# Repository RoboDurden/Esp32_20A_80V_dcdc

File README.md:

# Esp32_20A_80V_dcdc
 20A 80V dcdc/mppt with Esp32 and touch display

## KiCad pcb

## replaces lcd pickup module

https://www.aliexpress.com/item/1005004966830126.html

## KiCad circuit

## blender 3d models

## blender box / housing

## Arduino code (ssd1306)

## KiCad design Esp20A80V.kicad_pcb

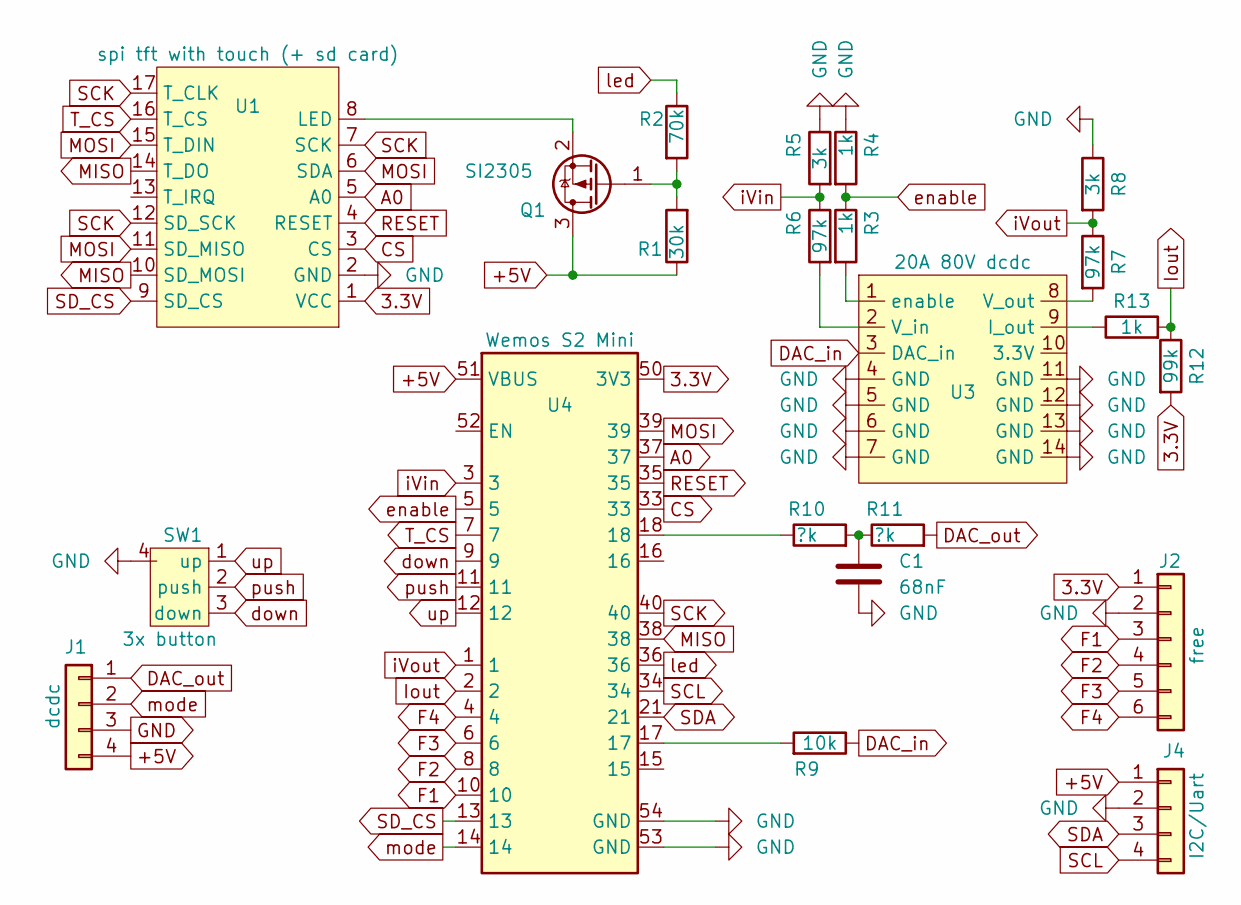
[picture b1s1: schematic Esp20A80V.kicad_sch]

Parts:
C1: 68nF; C_0805_2012Metric_Pad1.18x1.45mm_HandSolder
J1: dcdc; JST_PH_B4B-PH-K_1x04_P2.00mm_Vertical
J2: free; PinHeader_1x06_P2.54mm_Horizontal
J4: I2C/Uart; PinHeader_1x04_P2.54mm_Horizontal
Q1: SI2305; SOT-23
R1: 30k; R_0805_2012Metric_Pad1.20x1.40mm_HandSolder
R2: 70k; R_0805_2012Metric_Pad1.20x1.40mm_HandSolder
R3, R4, R13: 1k; R_0805_2012Metric_Pad1.20x1.40mm_HandSolder
R5, R8: 3k; R_0805_2012Metric_Pad1.20x1.40mm_HandSolder
R6, R7: 97k; R_0805_2012Metric_Pad1.20x1.40mm_HandSolder
R9: 10k; R_0805_2012Metric_Pad1.20x1.40mm_HandSolder
R10, R11: ?k; R_0805_2012Metric_Pad1.20x1.40mm_HandSolder
R12: 99k; R_0805_2012Metric_Pad1.20x1.40mm_HandSolder
SW1: 3x button; 3way dial switch
U1: spi tft with touch (+ sd card); display 128x160 +touch +sd
U3: 20A 80V dcdc; 20A80V dcdc
U4: Wemos S2 Mini

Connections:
3.3V: J2.1, R12.2, U1.1 (VCC), U4.50 (3V3)
+5V: J1.4, J4.1, Q1.3 (D), R1.1, U4.51 (VBUS)
A0: U1.5 (A0), U4.37
CS: U1.3 (CS), U4.33
DAC_in: R9.1, U3.3 (DAC_in)
DAC_out: J1.1, R11.2
F1: J2.3, U4.10
F2: J2.4, U4.8
F3: J2.5, U4.6
F4: J2.6, U4.4
GND: C1.2, J1.3, J2.2, J4.2, R4.1, R5.1, R8.1, SW1.4, U1.2 (GND), U3.4 (GND), U3.5 (GND), U3.6 (GND), U3.7 (GND), U3.11 (GND), U3.12 (GND), U3.13 (GND), U3.14 (GND), U4.53 (GND), U4.54 (GND)
Iout: R12.1, R13.2, U4.2
MISO: U1.10 (SD_MOSI), U1.14 (T_DO), U4.38
MOSI: U1.6 (SDA), U1.11 (SD_MISO), U1.15 (T_DIN), U4.39
unnamed: C1.1, R10.2, R11.1
unnamed: Q1.1 (G), R1.2, R2.2
unnamed: Q1.2 (S), U1.8 (LED)
unnamed: R9.2, U4.17
unnamed: R10.1, U4.18
unnamed: R13.1, U3.9 (I_out)
unnamed: R6.2, U3.2 (V_in)
unnamed: R7.2, U3.8 (V_out)
unnamed: R3.2, U3.1 (enable)
RESET: U1.4 (RESET), U4.35
SCK: U1.7 (SCK), U1.12 (SD_SCK), U1.17 (T_CLK), U4.40
SCL: J4.4, U4.34
SDA: J4.3, U4.21
SD_CS: U1.9 (SD_CS), U4.13
T_CS: U1.16 (T_CS), U4.7
down: SW1.3 (down), U4.9
enable: R3.1, R4.2, U4.5
iVin: R5.2, R6.1, U4.3
iVout: R7.1, R8.2, U4.1
led: R2.1, U4.36
mode: J1.2, U4.14
push: SW1.2 (push), U4.11
up: SW1.1 (up), U4.12

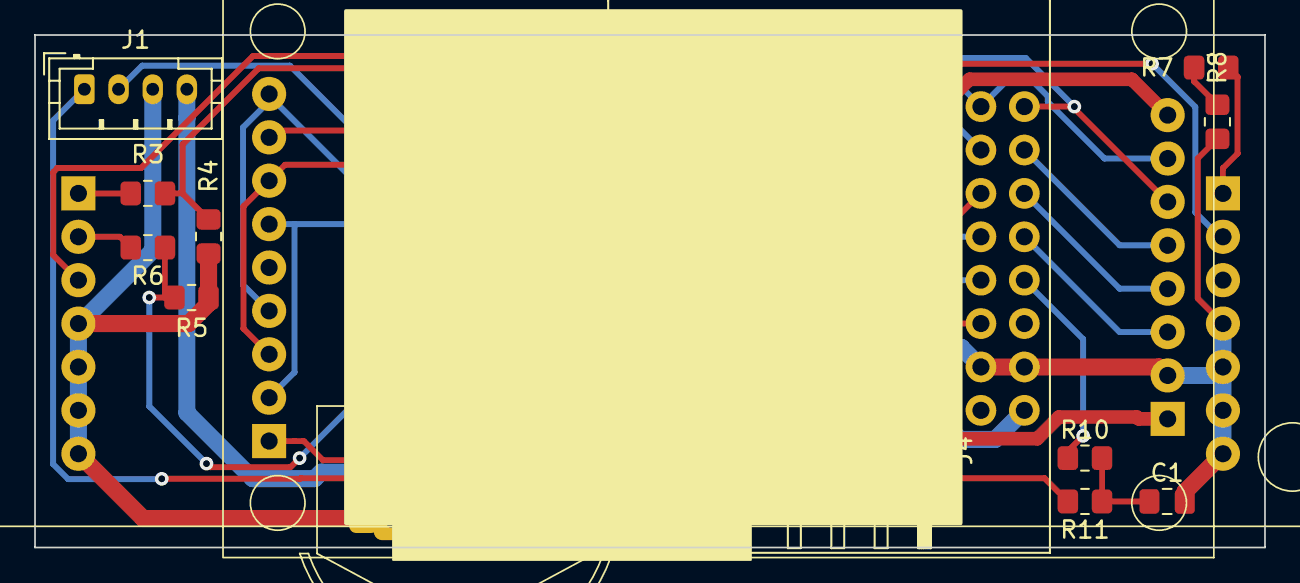
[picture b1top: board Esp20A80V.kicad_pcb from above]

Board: 2 copper layers, 72.0 x 30.0 mm, 22 parts (0 on the bottom side), 37 nets.

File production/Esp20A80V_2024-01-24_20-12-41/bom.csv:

Designator,Footprint,Quantity,Value,LCSC Part #
C1,0805,1,68nF,
J1,JST_PH_B4B-PH-K_1x04_P2.00mm_Vertical,1,dcdc,
J2,PinHeader_1x06_P2.54mm_Horizontal,1,free,
J4,PinHeader_1x04_P2.54mm_Horizontal,1,I2C/Uart,
Q1,SOT-23,1,SI2305,
R1,0805,1,30k,
"R10, R11",0805,2,?k,
R12,0805,1,99k,
"R13, R3, R4",0805,3,1k,
R2,0805,1,70k,
"R5, R8",0805,2,3k,
"R6, R7",0805,2,97k,
R9,0805,1,10k,
SW1,3way dial switch,1,3x button,
U1,display 128x160 +touch +sd,1,spi tft with touch (+ sd card),
U3,20A80V dcdc,1,20A 80V dcdc,
U4,Wemos S2 Mini,1,Wemos S2 Mini,

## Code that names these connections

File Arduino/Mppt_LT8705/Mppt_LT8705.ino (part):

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  pinMode(LED_BUILTIN, OUTPUT);

  pinMode(PIN_Uout,INPUT);
  pinMode(PIN_Iout,INPUT);

  //pinMode(PIN_DACin,INPUT);   // to not set an output hi or low level but analogOut
  
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
  pinMode(pin_Left, INPUT_PULLUP);
  pinMode(pin_Right, INPUT_PULLUP);
  pinMode(pin_Push, INPUT_PULLUP);

 
  // initialize digital pin LED_BUILTIN as an output.
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
  if (!digitalRead(pin_Left)) wButtons |= _ButtonDown;
  if (!digitalRead(pin_Right)) wButtons |= _ButtonUp;
  if (!digitalRead(pin_Push)) wButtons |= _ButtonPush;
  //OUT2N("wButtons",wButtons);

  if (g_sMess != "")
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    return true;
  }

  oDac.iOut -= 10;    // do not limit charging voltage by dac_out without overvoltage 
  CLAMP(oDac.iOut,DAC_OutMin,DAC_OutMax)
  
  if (oMpp.bOvervoltage)
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    }  
    case CONTROL_Uin:
    {
      oDac.iOut -= 10;    // do not limit charging voltage by dac_out without overvoltage 
      CLAMP(oDac.iOut,DAC_OutMin,DAC_OutMax)
      float fUDiff = oAdcLatest.fUin - oData.fUin;
      oDac.iIn += fUDiff / 4 + (fUDiff > 0 ? 1 : -1);
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{
  oAdcSum.iUin += analogRead(PIN_Uin);
  oAdcSum.iUout += analogRead(PIN_Uout);
  oAdcSum.iIout += analogRead(PIN_Iout);
  iAdcSum++;

  if (iNow < iTimeAdc)
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
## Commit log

2023-12-26 init
2024-01-23 footsprints verified and sd card added
2024-01-23 better circuit
2024-01-23 jst ph2.0 instead of dupont female
2024-01-25 jlpcb
